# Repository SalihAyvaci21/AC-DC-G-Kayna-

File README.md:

# AC-DC Güç Kaynağı (115-250V AC -> 24V 5A)

Bu proje, 115-250V AC girişten 24V DC / 5A çıkış sağlayan bir **izole AC-DC güç kaynağı** devresidir. Yüksek güç yoğunluğu, güvenlik ve verimlilik odaklı olarak tasarlanmıştır.

## 📦 Özellikler

- **Giriş Gerilimi:** 115V - 250V AC
- **Çıkış Gerilimi:** 24V DC
- **Çıkış Akımı:** 5A (maksimum)
- **Topoloji:** Half-Bridge
- **Güvenlik ve Koruma Özellikleri:**
  - Yüksek sıcaklık koruması
  - Sigorta (Fuse)
  - Gaz Deşarj Tüpü (GDT)
  - EMI/RFI Giriş Filtresi
  - Aşırı Gerilim için Shutdown devresi (>27V)

## ⚡ Tasarım Bileşenleri

### Güç Faktörü Düzeltme (PFC)
- **Kontrolcü:** L6563
- **Fonksiyon:** Giriş AC sinyalini düzeltir ve 400V DC seviyesine çıkarır.

### Anahtarlama Aşaması
- **Topoloji:** Half-Bridge Konfigürasyonu
- **Kontrolcü:** L6599D
- **MOSFET’ler:** STP20H100
- **Trafo:** Yalıtımlı ve yüksek frekanslı dönüşüm için tasarlanmıştır.

### Çıkış Doğrultma ve Regülasyon
- **Çıkış Doğrultması:** STP20H100 MOSFET ile yüksek verimli doğrultma
- **Geribildirim (Feedback):**
  - **Optokuplör:** LTV-817S ile izole çıkış voltajı kontrolü
  - **Shutdown Devresi:** BC847 transistörü ile 27V üzerindeki çıkışlar için devreyi kapatma

## 🔥 Koruma ve Filtreleme

- **Giriş Filtresi:** EMI ve RFI bastırma için LC filtre
- **Sigorta ve GDT:** Aşırı akım ve yıldırım darbelerine karşı koruma
- **Yüksek Sıcaklık Koruması:** Termistör/NTC ile izleme

## 📐 PCB Özellikleri

- **Katman Sayısı:** 2 katman
- **İzole Alanlar:** Yüksek gerilim ve düşük gerilim bölgeleri arasında güvenli izolasyon
- **Soğutma:** Güç bileşenleri için yeterli soğutma alanı ve heatsink montaj noktaları

## 🛠 Kullanım

1. **Bağlantı:**
   - Giriş: L, N, Toprak terminalleri üzerinden AC şebekeye bağlayın.
   - Çıkış: +24V ve GND terminallerinden yük bağlantısı yapın.

2. **Çalıştırma:**
   - Güçü açmadan önce bağlantıları kontrol edin.
   - İlk açılışta boşta test yapılması önerilir.

3. **Koruma Devreleri:**
   - Çıkış aşırı gerilim durumunda (>27V) devre BC847 tarafından kapatılır.
   - Aşırı akım veya kısa devre durumunda sigorta atar.

## 📁 Dosyalar

- `AC-DC Güç Kaynağı.kicad_pro` – KiCAD proje dosyası
- `AC-DC Güç Kaynağı.kicad_sch` – Devre şeması
- `AC-DC Güç Kaynağı.kicad_pcb` – PCB yerleşim dosyası
- `BOM.csv` – Parça listesi
- `Fabrikation_Toolkit` – Üretim için gerber dosyaları

## ⚠️ Dikkat

> Yüksek gerilim içeren bu devre **hayati tehlike** arz eder. Lütfen yalnızca deneyimli kişiler tarafından çalıştırılsın.

## 📜 Lisans

Bu proje açık kaynaklıdır ve kişisel/akademik kullanım için ücretsizdir.

---

AC-DC Power Supply (115-250V AC -> 24V 5A)
This project is an isolated AC-DC power supply circuit that converts 115-250V AC input to 24V DC / 5A output. It is designed for high power density, safety, and efficiency.

📦 Features
Input Voltage: 115V - 250V AC

Output Voltage: 24V DC

Output Current: 5A (maximum)

Topology: Half-Bridge

Safety and Protection Features:

Over-temperature protection

Fuse protection

Gas Discharge Tube (GDT)

EMI/RFI input filter

Shutdown circuit for overvoltage (>27V)

⚡ Design Components
Power Factor Correction (PFC)
Controller: L6563

Function: Rectifies the AC input and boosts it to 400V DC.

Switching Stage
Topology: Half-Bridge Configuration

Controller: L6599D

MOSFETs: STP20H100

Transformer: Designed for isolated, high-frequency power conversion.

Output Rectification and Regulation
Output Rectification: High-efficiency rectification using STP20H100 MOSFET

Feedback:

Optocoupler: LTV-817S for isolated output voltage control

Shutdown Circuit: BC847 transistor to shut down the system when output exceeds 27V

🔥 Protection and Filtering
Input Filter: LC filter for EMI and RFI suppression

Fuse and GDT: Protection against overcurrent and lightning surges

Over-Temperature Protection: Monitored via Thermistor/NTC

📐 PCB Features
Layer Count: 2 layers

Isolation Zones: Safe separation between high-voltage and low-voltage areas

Cooling: Sufficient area for heatsinks and power component thermal management

🛠 Usage
Connections:

Input: Connect to AC mains via L, N, and Ground terminals.

Output: Connect the load to +24V and GND terminals.

Operation:

Verify all connections before powering on.

Recommended to perform no-load testing on initial startup.

Protection Circuits:

The BC847 transistor shuts down the system if the output voltage exceeds 27V.

The fuse blows in case of overcurrent or short circuit.

📁 Files
AC-DC Güç Kaynağı.kicad_pro – KiCAD project file

AC-DC Güç Kaynağı.kicad_sch – Schematic file

AC-DC Güç Kaynağı.kicad_pcb – PCB layout file

Bomlist.xlsx – Bill of Materials

Fabrikation_Toolkit – Gerber files for manufacturing

⚠️ Warning
This circuit involves high voltages and poses a risk of electric shock. It should only be operated by experienced individuals.

📜 License
This project is open-source and free for personal/academic use.

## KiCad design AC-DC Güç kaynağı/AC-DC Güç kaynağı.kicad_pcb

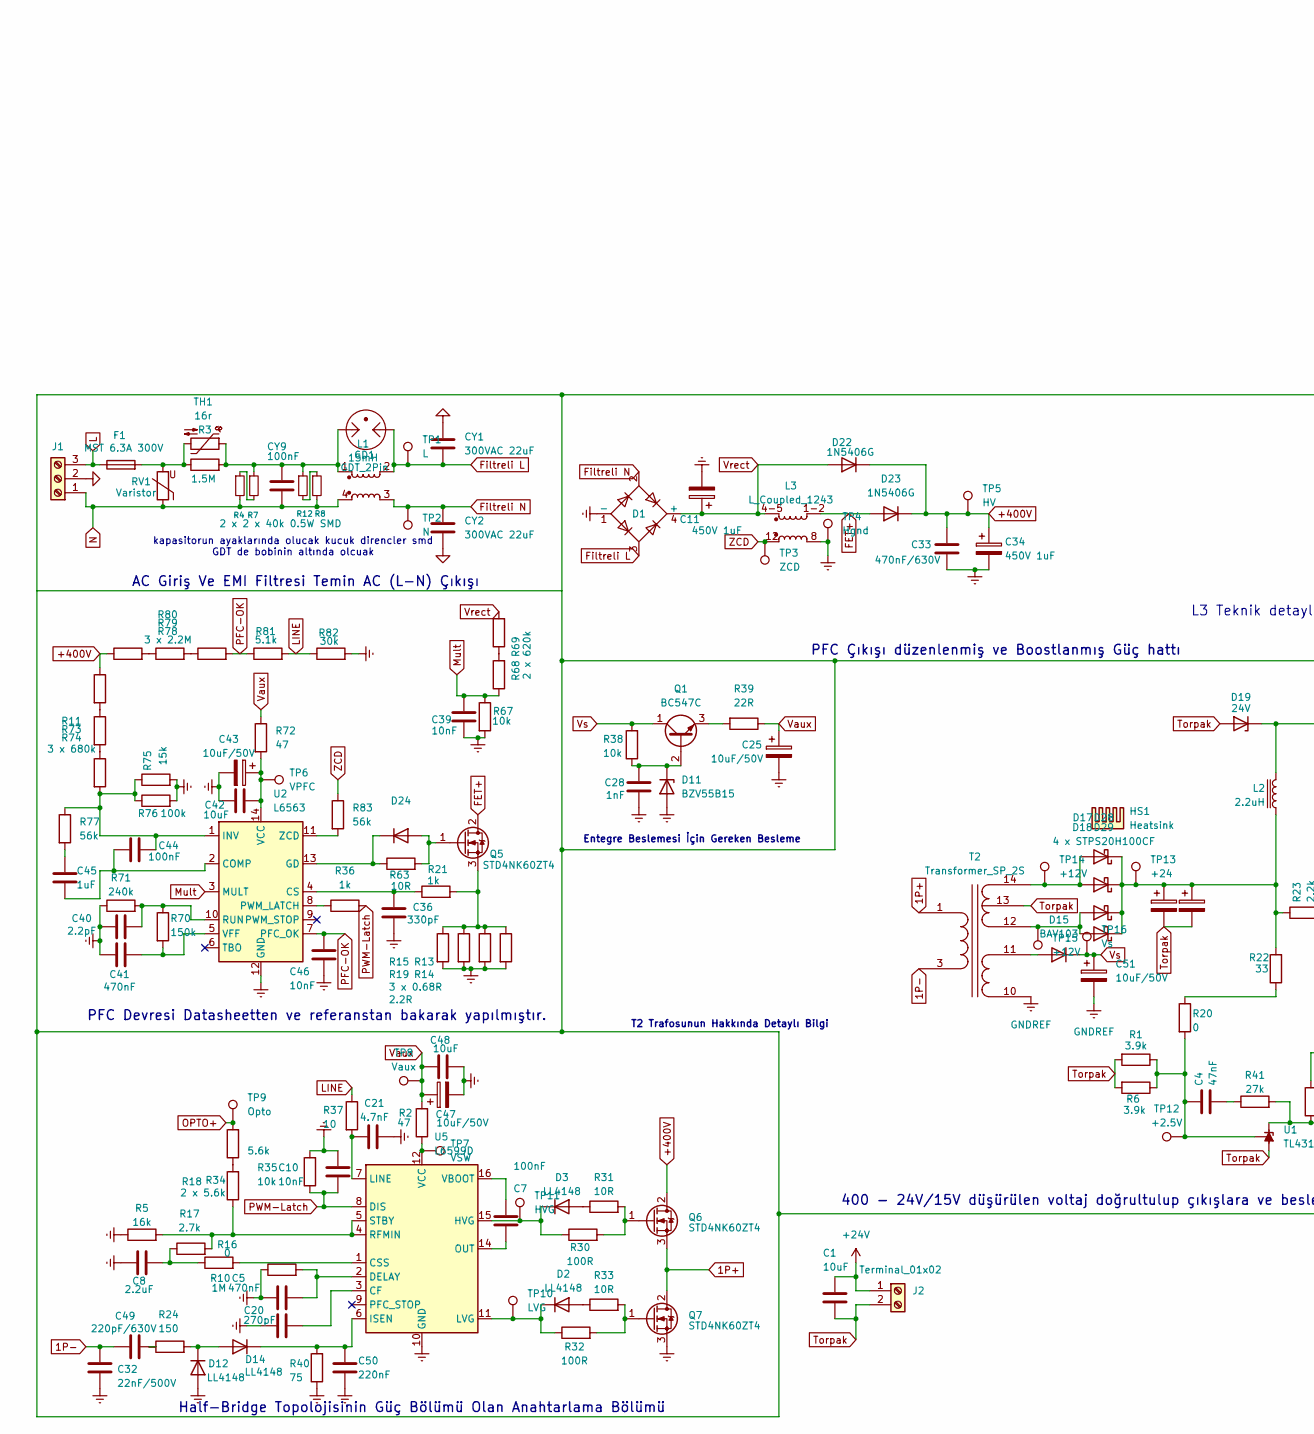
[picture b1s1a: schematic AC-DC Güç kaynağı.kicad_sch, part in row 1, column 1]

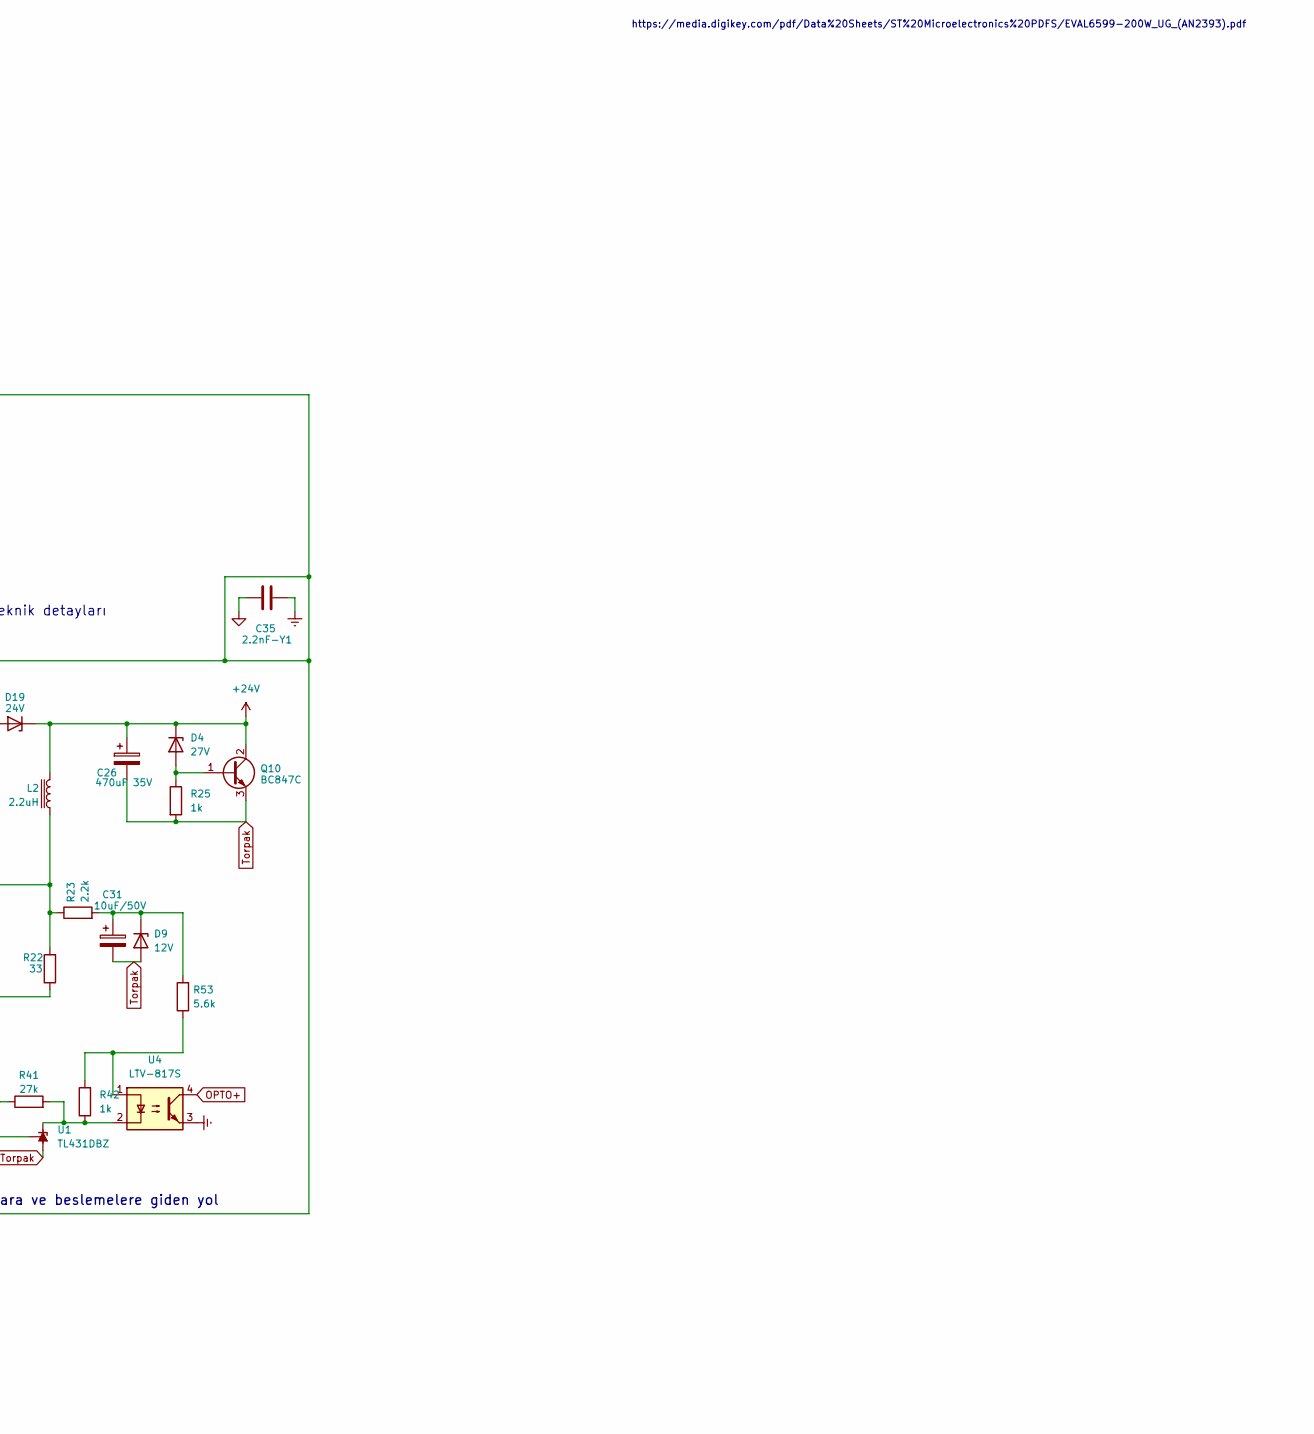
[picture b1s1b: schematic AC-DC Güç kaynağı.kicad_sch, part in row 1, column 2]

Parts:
C1, C42, C48: 10uF; C_1206_3216Metric_Pad1.33x1.80mm_HandSolder; Part Number CL31A106MBHNNNE
C4: 47nF; C_0603_1608Metric_Pad1.08x0.95mm_HandSolder; Part Number C0603C473K5RACTU
C5, C41: 470nF; C_0402_1005Metric_Pad0.74x0.62mm_HandSolder; Part Number GRM155R61H474KE11D
C7, C44: 100nF; C_0603_1608Metric_Pad1.08x0.95mm_HandSolder; Part Number 603-CC603KRX7R7BB104 Y
C8: 2.2uF; C_0603_1608Metric_Pad1.08x0.95mm_HandSolder; Part Number TMK107ABJ225KA-T
C10, C39, C46: 10nF; C_0603_1608Metric_Pad1.08x0.95mm_HandSolder; Part Number C0603C103K5RACTU
C11, C34: 450V 1uF; C_Radial_D8.0mm_H11.5mm_P3.50mm; Part Number UVR2W010MPD1TD
C14, C15, C26: 470uF 35V; C_Radial_D10.0mm_H16.0mm_P5.00mm; Part Number ESH477M035AH2AA
C20: 270pF; C_0603_1608Metric_Pad1.08x0.95mm_HandSolder; Part Number CL10C271JB81PNC
C21: 4.7nF; C_0603_1608Metric_Pad1.08x0.95mm_HandSolder; Part Number CC0603KRX7R9BB472
C25, C31, C43, C47, C51: 10uF/50V; C_Radial_D5.0mm_H7.0mm_P2.00mm; Part Number ESK106M050AC3AA
C28: 1nF; C_0603_1608Metric_Pad1.08x0.95mm_HandSolder; Part Number UMK107BJ105KA-T
C32: 22nF/500V; C_1206_3216Metric_Pad1.33x1.80mm_HandSolder; Part Number C1206C223KCRACAUTO
C33: 470nF/630V; C_Radial_D5.0mm_H7.0mm_P2.00mm; Part Number 46KI24700001K
C35: 2.2nF-Y1; C_Radial_D10.0mm_H16.0mm_P5.00mm; Part Number C751U222MWWDAAWL50
C36: 330pF; C_0603_1608Metric_Pad1.08x0.95mm_HandSolder; Part Number KGM15AR71E331KT
C40: 2.2pF; C_0603_1608Metric; Part Number CC0603BRNPO0BN2R2
C45: 1uF; C_0603_1608Metric_Pad1.08x0.95mm_HandSolder; Part Number UMK107BJ105KA-T
C49: 220pF/630V; C_0805_2012Metric; Part Number CC0805JRNPOZBN221
C50: 220nF; C_0805_2012Metric_Pad1.18x1.45mm_HandSolder; Part Number C0805C224K5RACTU
CY1, CY2: 300VAC 22uF; C_Radial_D8.0mm_H11.5mm_P3.50mm; Part Number DE2E3SA222MA3BX02F
CY9: 100nF; C_Rect_L18.0mm_W6.0mm_P15.00mm_FKS3_FKP3; Part Number 890324025017CS
D1: GBU8J; Diode_Bridge_Vishay_GBU; Part Number GBU8J
D2, D3, D12, D14, D24: LL4148; D_MiniMELF_Handsoldering; Part Number LL4148
D4: 27V; D_MiniMELF_Handsoldering; Part Number BZV55-B27,115
D9: 12V; D_MiniMELF_Handsoldering; Part Number BZV55-B12,115
D11: BZV55B15; D_MiniMELF_Handsoldering; Part Number BZV55-B15,115
D15: BAV103; D_MiniMELF_Handsoldering; Part Number BAV103
D17, D29: STPS20H100CF; TO-220-2_Horizontal_TabDown; Part Number MBR30200CT
D18: 2 x STPS20H100CF; TO-220-2_Horizontal_TabDown; Part Number MBR30200CT
D19: 24V; D_MiniMELF_Handsoldering; Part Number 771-BZV55-B24115
D22, D23: 1N5406G; D_DO-201AD_P12.70mm_Horizontal; Part Number 1N5406G
D28: 4 x STPS20H100CF; TO-220-2_Horizontal_TabDown; Part Number MBR30200CT
F1: MST 6.3A 300V; C_Rect_L9.0mm_W4.0mm_P7.50mm_MKT; Part Number RSTA 6.3 BULK
GD1: GDT_2Pin; Transformer_Wurth_WE-AGDT-EP7; Part Number 2003-35-SM-RPLF
HS1: Heatsink; Heatsink_125x35x50mm_3xFixationM3
J1: Screw_Terminal_01x03; TerminalBlock_Altech_AK300-3_P5.00mm
J2: Terminal_01x02; TerminalBlock_Altech_AK300-2_P5.00mm
L1: 15mH; EH24-3.0-02-1M2; Part Number EH24-3.0-02-1M2
L2: 2.2uH; Fuse_Littelfuse_372_D8.50mm; Part Number SBC3-2R2-602
L3: L_Coupled_1243
Q1: BC547C; TO-92Flat; Part Number BC547C
Q5, Q6, Q7: STD4NK60ZT4; TO-252-2; Part Number STD4NK60ZT4
Q10: BC847C; SOT-23-3; Part Number BC847C
R1, R6: 3.9k; R_1206_3216Metric_Pad1.30x1.75mm_HandSolder; Part Number RMCF1206FT3K90
R2, R72: 47; R_Axial_DIN0207_L6.3mm_D2.5mm_P10.16mm_Horizontal; Part Number FMP100JR-52-47R
R3: 1.5M; R_Axial_DIN0309_L9.0mm_D3.2mm_P12.70mm_Horizontal; Part Number ROX5SJ22R
R4: 2 x 2 x 40k 0.5W SMD; R_1206_3216Metric; Part Number RNCP1206FTD40K2TR-ND
R5: 16k; R_1206_3216Metric_Pad1.30x1.75mm_HandSolder; Part Number RC0805FR-0716KL
R7, R8, R12: 40k 0.5W SMD; R_1206_3216Metric; Part Number RNCP1206FTD40K2TR-ND
R10: 1M; R_0805_2012Metric_Pad1.20x1.40mm_HandSolder; Part Number RG2012P-105-D-T5
R11, R74: 680k; R_1206_3216Metric; Part Number RC1206FR-07680KL
R13: 2.2R; R_1206_3216Metric; Part Number RMCF1206FT2R20
R14, R15: 0.68R; R_1206_3216Metric; Part Number ERJ-8RQFR68V
R16, R20: 0; R_1206_3216Metric
R17: 2.7k; R_1206_3216Metric_Pad1.30x1.75mm_HandSolder; Part Number AC1206FR-072K7L
R18: 2 x 5.6k; C_1206_3216Metric_Pad1.33x1.80mm_HandSolder; Part Number CRGCQ1206F5K6
R19: 3 x 0.68R; R_1206_3216Metric; Part Number ERJ-8RQFR68V
R21, R25, R36, R42: 1k; R_1206_3216Metric_Pad1.30x1.75mm_HandSolder; Part Number RNCP1206FTD1K00
R22: 33; R_1206_3216Metric_Pad1.30x1.75mm_HandSolder; Part Number CRCW120633R0FKEAC
R23: 2.2k; R_1206_3216Metric_Pad1.30x1.75mm_HandSolder; Part Number CRGCQ1206F2K2
R24: 150; R_1206_3216Metric_Pad1.30x1.75mm_HandSolder; Part Number RC1206FR-07150RL
R30, R32: 100R; R_1206_3216Metric_Pad1.30x1.75mm_HandSolder; Part Number RC1206FR-07100RL
R31, R33, R63: 10R; R_1206_3216Metric_Pad1.30x1.75mm_HandSolder; Part Number RMCF1206FT10R0
R34, R53: 5.6k; R_1206_3216Metric_Pad1.30x1.75mm_HandSolder; Part Number CRGCQ1206F5K6
R35, R38, R67: 10k; R_1206_3216Metric_Pad1.30x1.75mm_HandSolder; Part Number RC1206FR-0715RL
R37: 10; R_1206_3216Metric_Pad1.30x1.75mm_HandSolder; Part Number RMCF1206FT10R0
R39: 22R; R_1206_3216Metric_Pad1.30x1.75mm_HandSolder; Part Number RC1206JR-0722RL
R40: 75; R_1206_3216Metric_Pad1.30x1.75mm_HandSolder; Part Number RMCF1206FT10R0
R41: 27k; R_1206_3216Metric_Pad1.30x1.75mm_HandSolder; Part Number RC1206JR-0727KL
R68: 620k; R_1206_3216Metric_Pad1.30x1.75mm_HandSolder; Part Number RC1206FR-07620KL
R69: 2 x 620k; R_1206_3216Metric; Part Number RC1206FR-07620KL
R70: 150k; R_1206_3216Metric_Pad1.30x1.75mm_HandSolder; Part Number RC1206FR-07150KL
R71: 240k; R_1206_3216Metric_Pad1.30x1.75mm_HandSolder; Part Number RC1206JR-07240KL
R73: 3 x 680k; R_1206_3216Metric; Part Number RC1206FR-07680KL
R75: 15k; R_1206_3216Metric_Pad1.30x1.75mm_HandSolder; Part Number RMCF1206JT15K0
R76: 100k; R_0805_2012Metric_Pad1.20x1.40mm_HandSolder; Part Number RG2012P-104-B-T5
R77, R83: 56k; R_1206_3216Metric_Pad1.30x1.75mm_HandSolder; Part Number RMCF1206JT56K0
R78, R80: 2.2M; R_1206_3216Metric; Part Number CRCW12062M20FKEA
R79: 3 x 2.2M; R_1206_3216Metric; Part Number CRCW12062M20FKEA
R81: 5.1k; R_1206_3216Metric_Pad1.30x1.75mm_HandSolder; Part Number RMCF1206JT5K10
R82: 30k; R_0805_2012Metric_Pad1.20x1.40mm_HandSolder; Part Number RMCF0805FT30K0
RV1: Varistor; RV_Disc_D7mm_W3.6mm_P5mm; Part Number B72210P2271K101
T2: Transformer_SP_2S; Trafo
TH1: 16r; CP_Radial_D5.0mm_P2.50mm; Part Number 954-10D2-07LD
TP1: L; TestPoint_Keystone_5000-5004_Miniature
TP2: N; TestPoint_Keystone_5000-5004_Miniature
TP3: ZCD; TestPoint_Keystone_5000-5004_Miniature
TP4: Hgnd; TestPoint_Keystone_5000-5004_Miniature
TP5: HV; TestPoint_Keystone_5000-5004_Miniature
TP6: VPFC; TestPoint_Keystone_5000-5004_Miniature
TP7: VSW; TestPoint_Keystone_5000-5004_Miniature
TP8: Vaux; TestPoint_Keystone_5000-5004_Miniature
TP9: Opto; TestPoint_Keystone_5000-5004_Miniature
TP10: LVG; TestPoint_Keystone_5000-5004_Miniature
TP11: HVG; TestPoint_Keystone_5000-5004_Miniature
TP12: +2.5V; TestPoint_Keystone_5000-5004_Miniature
TP13: +24; TestPoint_Keystone_5000-5004_Miniature
TP14, TP15: +12V; TestPoint_Keystone_5000-5004_Miniature
TP16: Vs; TestPoint_Keystone_5000-5004_Miniature
U1: TL431DBZ; SOT-23; Part Number TL431
U2: L6563; SOIC-14_3.9x8.7mm_P1.27mm; Part Number L6563
U4: LTV-817S; SMDIP-4_W9.53mm
U5: L6599D; SO-16_5.3x10.2mm_P1.27mm; Part Number L6599N

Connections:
1P+: Q6.3 (S), Q7.2 (D), T2.1 (IN+)
1P-: C32.2, C49.2, T2.3 (IN-)
+24V: C1.1, C26.1, D4.1 (K), D19.1 (K), J2.1, L2.2, Q10.2 (C)
+400V: C33.1, C34.1, D22.1 (K), D23.1 (K), L3.1, L3.2, Q6.2 (D), R11.1, R78.1, TP5.1; also elsewhere on the board
FET+: D23.2 (A), L3.1-2 (2), Q5.2 (D)
Filtreli L: CY1.2, D1.3, GD1.1, L1.2, TP1.1; also elsewhere on the board
Filtreli N: CY2.1, D1.2, L1.3, TP2.1; also elsewhere on the board
GND: C35.1, CY1.1, CY2.2, J1.2
GNDREF: C5.1, C8.1, C10.2, C11.2, C20.1, C21.2, C25.2, C28.2, C32.1, C33.2, C34.2, C35.2, C36.2, C39.2, C40.1, C41.1, C42.1, C43.2, C46.1, C47.2, C48.1, C50.1, C51.2, D1.1 (-), D11.2 (A), D12.2 (A), L3.8 (3), Q7.3 (S), R5.1, R10.1, R13.2, R14.2, R15.2, R19.2, R35.2, R40.1, R67.2, R71.1, R75.2, R76.2, R82.2, T2.10 (OUT2B), TP4.1, U2.12 (GND), U4.3, U5.10 (GND)
L: F1.1, J1.3
LINE: R37.1, R81.2, R82.1
Mult: C39.1, R67.1, R68.1, U2.3 (MULT)
N: CY9.2, J1.1, L1.4, R4.2, R8.2, RV1.1
unnamed: C4.1, R41.1
unnamed: C8.2, R16.1, R17.1
unnamed: C45.1, R77.2
unnamed: C49.1, R24.1
unnamed: CY9.1, GD1.3, L1.1, R3.2, R7.1, R12.1, TH1.1
unnamed: D2.2 (A), R33.1
unnamed 19: D2.1 (K), R32.1, TP10.1, U5.11 (LVG); also elsewhere on the board
unnamed: D3.2 (A), R31.1
unnamed 21: D3.1 (K), R30.1, TP11.1, U5.15 (HVG); also elsewhere on the board
unnamed: D4.2 (A), Q10.1 (B), R25.1
unnamed: C31.1, D9.1 (K), R23.2, R53.2
unnamed: C28.1, D11.1 (K), Q1.2 (B), R38.1
unnamed: D12.1 (K), D14.2 (A), R24.2
unnamed: C50.2, D14.1 (K), R40.2, U5.6 (ISEN)
unnamed: D15.2 (A), T2.11 (OUT2A)
unnamed 28: D17.2 (A), D28.2 (A), T2.14 (OUT1A), TP14.1; also elsewhere on the board
unnamed: C14.1, C15.1, D17.1 (K), D18.1 (K), D28.1 (K), D29.1 (K), L2.1, R22.2, R23.1, TP13.1
unnamed 30: D18.2 (A), D29.2 (A), T2.12 (OUT1B), TP15.1; also elsewhere on the board
unnamed: D24.2 (A), Q5.1 (G), R63.2
unnamed: D24.1 (K), R63.1, U2.13 (GD)
unnamed: F1.2, R3.1, RV1.2, TH1.2
unnamed: Q1.3 (E), R39.2
unnamed: Q5.3 (S), R13.1, R14.1, R15.1, R19.1, R21.2
unnamed: Q6.1 (G), R30.2, R31.2
unnamed: Q7.1 (G), R32.2, R33.2
unnamed: R4.1, R7.2
unnamed: R11.2, R73.1
unnamed: R8.1, R12.2
unnamed: R18.2, R34.1
unnamed: R20.1, R22.1
unnamed: R42.2, R53.1, U4.1
unnamed: R68.2, R69.1
unnamed: R73.2, R74.1
unnamed: R78.2, R79.1
unnamed: R79.2, R80.1
unnamed: R41.2, R42.1, U1.1 (K), U4.2
unnamed: C4.2, R1.1, R6.1, R20.2, TP12.1, U1.2 (REF)
unnamed: C44.2, C45.2, U2.2 (COMP)
unnamed: C36.1, R21.1, U2.4 (CS)
unnamed: C44.1, R74.2, R75.1, R76.1, R77.1, U2.1 (INV)
unnamed: R36.1, U2.8 (PWM_LATCH)
unnamed: C40.2, R70.1, R71.2, U2.10 (RUN)
unnamed 55: C42.2, C43.1, R72.2, TP6.1, U2.14 (VCC); also elsewhere on the board
unnamed: C41.2, R70.2, U2.5 (VFF)
unnamed: R83.2, U2.11 (ZCD)
unnamed: C20.2, U5.3 (CF)
unnamed: R16.2, U5.1 (CSS)
unnamed: C5.2, R10.2, U5.2 (DELAY)
unnamed: C21.1, R37.2, U5.7 (LINE)
unnamed: C7.2, U5.14 (OUT)
unnamed: R5.2, R17.2, R18.1, U5.4 (RFMIN), U5.5 (STBY)
unnamed: C7.1, U5.16 (VBOOT)
unnamed 65: R2.1, TP7.1, U5.12 (VCC); also elsewhere on the board
OPTO+: R34.2, TP9.1, U4.4; also elsewhere on the board
PFC-OK: C46.2, R80.2, R81.1, U2.7 (PFC_OK)
PWM-Latch: C10.1, R35.1, R36.2, U5.8 (DIS)
Torpak: C1.2, C14.2, C15.2, C26.2, C31.2, D9.2 (A), D19.2 (A), J2.2, Q10.3 (E), R1.2, R6.2, R25.2, T2.13 (PM), U1.3 (A)
Vaux: C25.1, C47.1, C48.2, R2.2, R39.1, R72.1, TP8.1
Vrect: C11.1, D1.4 (+), D22.2 (A), L3.4, L3.4-5 (1), L3.5, R69.2
Vs: C51.1, D15.1 (K), Q1.1 (C), R38.2, TP16.1; also elsewhere on the board
ZCD: L3.12 (4), R83.1, TP3.1

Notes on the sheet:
kapasitorun ayaklarında olucak kucuk direncler smd GDT de bobinin altında olcuak
PFC Devresi Datasheetten ve referanstan bakarak yapılmıştır.
PFC Çıkışı düzenlenmiş ve Boostlanmış Güç hattı
https://media.digikey.com/pdf/Data%20Sheets/ST%20Microelectronics%20PDFS/EVAL6599-200W_UG_(AN2393).pdf
Half-Bridge Topolojisinin Güç Bölümü Olan Anahtarlama Bölümü
L3 Teknik detayları
AC Giriş Ve EMI Filtresi Temin AC (L-N) Çıkışı
Entegre Beslemesi İçin Gereken Besleme
400 - 24V/15V düşürülen voltaj doğrultulup çıkışlara ve beslemelere giden yol
T2 Trafosunun Hakkında Detaylı Bilgi

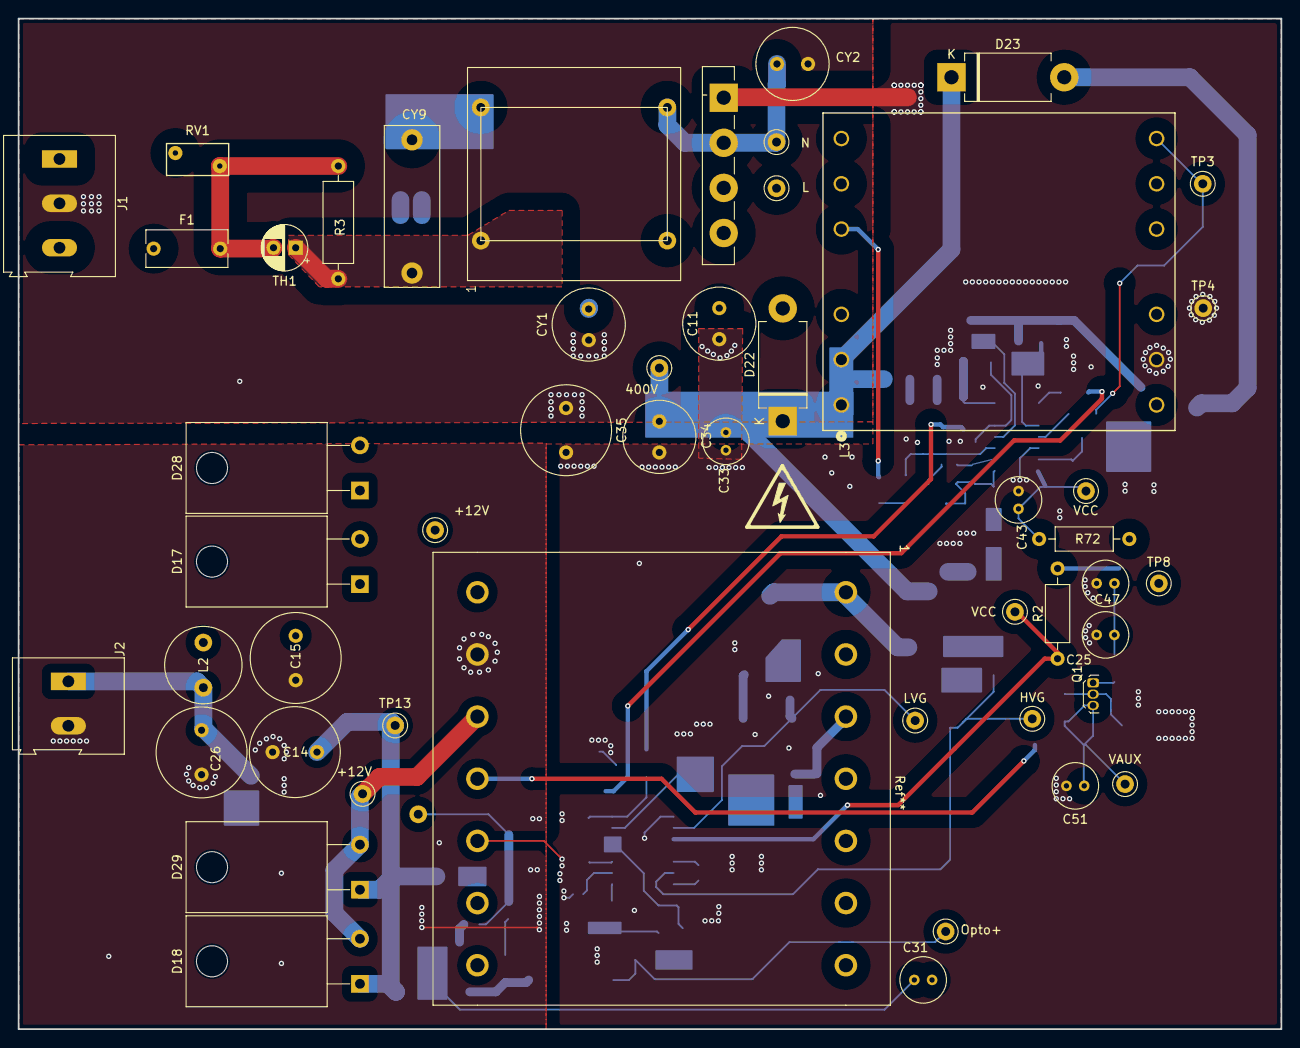
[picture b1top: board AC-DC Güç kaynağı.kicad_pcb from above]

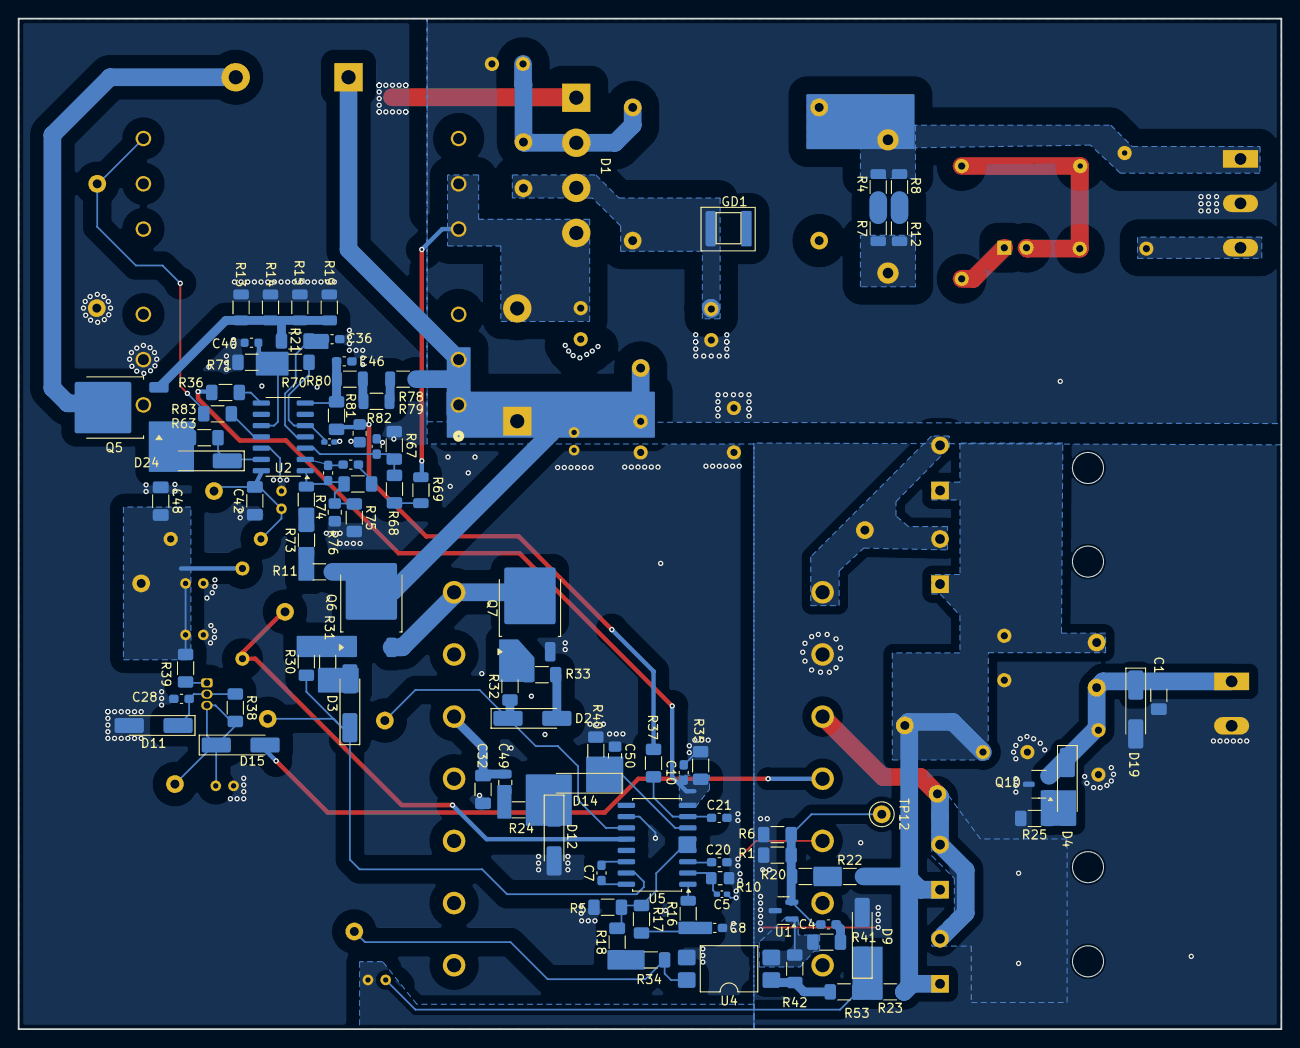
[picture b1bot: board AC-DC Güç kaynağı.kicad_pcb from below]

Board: 2 copper layers, 142.2 x 113.8 mm, 144 parts (94 on the bottom side), 74 nets.

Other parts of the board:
400V: HV; TestPoint_Keystone_5000-5004_Miniature
+12V, +12V#2: +12V; TestPoint_Keystone_5000-5004_Miniature
HVG: HVG; TestPoint_Keystone_5000-5004_Miniature
L: L; TestPoint_Keystone_5000-5004_Miniature
LVG: LVG; TestPoint_Keystone_5000-5004_Miniature
N: N; TestPoint_Keystone_5000-5004_Miniature
Opto+: Opto; TestPoint_Keystone_5000-5004_Miniature
VAUX: Vs; TestPoint_Keystone_5000-5004_Miniature
VCC: VSW; TestPoint_Keystone_5000-5004_Miniature
VCC#2: VPFC; TestPoint_Keystone_5000-5004_Miniature

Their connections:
+400V: 400V.1; also elsewhere on the board
Filtreli L: L.1; also elsewhere on the board
Filtreli N: N.1; also elsewhere on the board
unnamed 19: LVG.1; also elsewhere on the board
unnamed 21: HVG.1; also elsewhere on the board
unnamed 28: +12V#2.1; also elsewhere on the board
unnamed 30: +12V.1; also elsewhere on the board
unnamed 55: VCC#2.1; also elsewhere on the board
unnamed 65: VCC.1; also elsewhere on the board
OPTO+: Opto+.1; also elsewhere on the board
Vs: VAUX.1; also elsewhere on the board

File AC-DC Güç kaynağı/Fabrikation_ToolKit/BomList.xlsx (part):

'Reference' | 'Value' | 'Qty' | 'Part Number' | 'supplier part number' | 'supplier' | 'Footprint'
'C1,C42,C48' | '10uF' | '3' | 'CL31A106MBHNNNE' | '187-CL31A106MBHNNNE' | mouser' | 'Capacitor_SMD:C_1206_3216Metric_Pad1.33x1.80mm_HandSolder'
'C4' | '47nF' | '1' | ' C0603C473K5RACTU' | '80-C0603C473K5R' | mouser' | 'Capacitor_SMD:C_0603_1608Metric_Pad1.08x0.95mm_HandSolder'
'C5,C41' | '470nF' | '2' | ' GRM155R61H474KE11D' | '81-GRM155R61H474KE1D' | mouser' | 'Capacitor_SMD:C_0402_1005Metric_Pad0.74x0.62mm_HandSolder'
'C7,C44' | '100nF' | '2' | '603-CC603KRX7R7BB104 Y' | 'CC0603KRX7R7BB104' | mouser' | 'Capacitor_SMD:C_0603_1608Metric_Pad1.08x0.95mm_HandSolder'
'C8' | '2.2uF' | '1' | 'TMK107ABJ225KA-T' | '963-TMK107ABJ225KA-T ' | mouser' | 'Capacitor_SMD:C_0603_1608Metric_Pad1.08x0.95mm_HandSolder'
'C10,C39,C46' | '10nF' | '3' | 'C0603C103K5RACTU' | '80-C0603C103K5R' | mouser' | 'Capacitor_SMD:C_0603_1608Metric_Pad1.08x0.95mm_HandSolder'
'C11,C34' | '450V 1uF' | '2' | ' UVR2W010MPD1TD' | '647-UVR2W010MPD1TD' | mouser' | 'Capacitor_THT:C_Radial_D8.0mm_H11.5mm_P3.50mm'
'C14,C15,C26' | '470uF 35V' | '3' | ' ESH477M035AH2AA' | '80-ESH477M035AH2AA' | mouser' | 'Capacitor_THT:C_Radial_D10.0mm_H16.0mm_P5.00mm'
'C20' | '270pF' | '1' | 'CL10C271JB81PNC' | '187-CL10C271JB81PNC' | mouser' | 'Capacitor_SMD:C_0603_1608Metric_Pad1.08x0.95mm_HandSolder'
'C21' | '4.7nF' | '1' | 'CC0603KRX7R9BB472' | '603-C0603KRX7R9BB472' | mouser' | 'Capacitor_SMD:C_0603_1608Metric_Pad1.08x0.95mm_HandSolder'
'C25,C31,C43,C47,C51' | '10uF/50V' | '5' | ' ESK106M050AC3AA' | '80-ESK106M050AC3AA ' | mouser' | 'Capacitor_THT:C_Radial_D5.0mm_H7.0mm_P2.00mm'
'C28' | '1nF' | '1' | 'UMK107BJ105KA-T' | '963-UMK107BJ105KA-T' | mouser' | 'Capacitor_SMD:C_0603_1608Metric_Pad1.08x0.95mm_HandSolder'
'C32' | '22nF/500V' | '1' | 'C1206C223KCRACAUTO' | '80-C1206C223KCRAUTO' | mouser' | 'Capacitor_SMD:C_1206_3216Metric_Pad1.33x1.80mm_HandSolder'
'C33' | '470nF/630V' | '1' | '46KI24700001K' | '80-R46KI24700001K' | mouser' | 'Capacitor_THT:C_Radial_D5.0mm_H7.0mm_P2.00mm'
'C35' | '2.2nF-Y1' | '1' | 'C751U222MWWDAAWL50' | '80-C751U222MWWDAWL50' | mouser' | 'Capacitor_THT:C_Radial_D10.0mm_H16.0mm_P5.00mm'
'C36' | '330pF' | '1' | ' KGM15AR71E331KT' | '581-KGM15AR71E331KT' | mouser' | 'Capacitor_SMD:C_0603_1608Metric_Pad1.08x0.95mm_HandSolder'
'C40' | '2.2pF' | '1' | ' CC0603BRNPO0BN2R2' | '603-CC0603BNPO0BN2R2' | mouser' | 'Capacitor_SMD:C_0603_1608Metric'
'C45' | '1uF' | '1' | 'UMK107BJ105KA-T' | '963-UMK107BJ105KA-T' | mouser' | 'Capacitor_SMD:C_0603_1608Metric_Pad1.08x0.95mm_HandSolder'
'C49' | '220pF/630V' | '1' | 'CC0805JRNPOZBN221' | '603-CC805JRNPOZBN221' | mouser' | 'Capacitor_SMD:C_0805_2012Metric'
'C50' | '220nF' | '1' | ' C0805C224K5RACTU' | '80-C0805C224K5R' | mouser' | 'Capacitor_SMD:C_0805_2012Metric_Pad1.18x1.45mm_HandSolder'
'CY1,CY2' | '300VAC 22uF' | '2' | 'DE2E3SA222MA3BX02F' | '490-DE2E3SA222MA3BX02F-ND' | mouser' | 'Capacitor_THT:C_Radial_D8.0mm_H11.5mm_P3.50mm'
'CY9' | '100nF' | '1' | '890324025017CS' | '710-890324025017CS' | mouser' | 'Capacitor_THT:C_Rect_L18.0mm_W6.0mm_P15.00mm_FKS3_FKP3'
'D1' | 'GBU8J' | '1' | 'GBU8J' | '637-GBU8J' | mouser' | 'Diode_THT:Diode_Bridge_Vishay_GBU'
'D2,D3,D12,D14,D24' | 'LL4148' | '5' | 'LL4148' | '637-LL4148' | mouser' | 'Diode_SMD:D_MiniMELF_Handsoldering'
'D4' | '27V' | '1' | 'BZV55-B27,115' | '771-BZV55-B27115' | mouser' | 'Diode_SMD:D_MiniMELF_Handsoldering'
'D9' | '12V' | '1' | 'BZV55-B12,115' | '771-BZV55-B12115' | mouser' | 'Diode_SMD:D_MiniMELF_Handsoldering'
'D11' | 'BZV55B15' | '1' | 'BZV55-B15,115' | '771-BZV55-B15-T/R' | mouser' | 'Diode_SMD:D_MiniMELF_Handsoldering'
'D15' | 'BAV103' | '1' | 'BAV103' | '512-BAV103' | mouser' | 'Diode_SMD:D_MiniMELF_Handsoldering'
'D17,D29' | 'STPS20H100CF' | '2' | 'MBR30200CT' | '637-MBR30200CT' | mouser' | 'Package_TO_SOT_THT:TO-220-2_Horizontal_TabDown'
'D18' | '2 x STPS20H100CF' | '1' | 'MBR30200CT' | '637-MBR30200CT' | mouser' | 'Package_TO_SOT_THT:TO-220-2_Horizontal_TabDown'
'D19' | '24V' | '1' | '771-BZV55-B24115' | '771-BZV55-B24115' | mouser' | 'Diode_SMD:D_MiniMELF_Handsoldering'
'D22,D23' | '1N5406G' | '2' | '1N5406G' | '863-1N5406G' | mouser' | 'Diode_THT:D_DO-201AD_P12.70mm_Horizontal'
'D28' | '4 x STPS20H100CF' | '1' | 'MBR30200CT' | '637-MBR30200CT' | mouser' | 'Package_TO_SOT_THT:TO-220-2_Horizontal_TabDown'
'F1' | 'MST 6.3A 300V' | '1' | 'RSTA 6.3 BULK' | '530-RSTA6.3BULK' | mouser' | 'Capacitor_THT:C_Rect_L9.0mm_W4.0mm_P7.50mm_MKT'
'GD1' | 'GDT_2Pin' | '1' | '2003-35-SM-RPLF' | '652-2003-35-SM-RPLF' | mouser' | 'Transformer_SMD:Transformer_Wurth_WE-AGDT-EP7'
'HS1' | 'Heatsink' | '1' | '' | '' | mouser' | 'Heatsink:Heatsink_125x35x50mm_3xFixationM3'
'J1' | 'Screw_Terminal_01x03' | '1' | '' | '' | mouser' | 'TerminalBlock:TerminalBlock_Altech_AK300-3_P5.00mm'
'J2' | 'Terminal_01x02' | '1' | '' | '' | mouser' | 'TerminalBlock:TerminalBlock_Altech_AK300-2_P5.00mm'
'L1' | '15mH' | '1' | 'EH24-3.0-02-1M2' | '631-EH24-3.0-02-1M2' | mouser' | 'Library:EH24-3.0-02-1M2'
'L2' | '2.2uH' | '1' | 'SBC3-2R2-602' | '80-SBC3-2R2-602' | mouser' | 'Fuse:Fuse_Littelfuse_372_D8.50mm'
'L3' | 'L_Coupled_1243' | '1' | '' | '' | mouser' | ''
'Q1' | 'BC547C' | '1' | 'BC547C' | '637-BC547C' | mouser' | 'Package_TO_SOT_THT:TO-92Flat'
'Q5,Q6,Q7' | 'STD4NK60ZT4' | '3' | 'STD4NK60ZT4' | '511-STD4NK60Z' | mouser' | 'Package_TO_SOT_SMD:TO-252-2'
'Q10' | 'BC847C' | '1' | 'BC847C' | '637-BC847C' | mouser' | 'Package_TO_SOT_SMD:SOT-23-3'
'R1,R6' | '3.9k' | '2' | 'RMCF1206FT3K90' | '708-RMCF1206FT3K90' | mouser' | 'Resistor_SMD:R_1206_3216Metric_Pad1.30x1.75mm_HandSolder'
'R2,R72' | '47' | '2' | 'FMP100JR-52-47R' | '603-FMP100JR-52-47R' | mouser' | 'Resistor_THT:R_Axial_DIN0207_L6.3mm_D2.5mm_P10.16mm_Horizontal'
'R3' | '1.5M' | '1' | 'ROX5SJ22R' | '279-ROX5SJ22R' | mouser' | 'Resistor_THT:R_Axial_DIN0309_L9.0mm_D3.2mm_P12.70mm_Horizontal'
'R4' | '2 x 2 x 40k 0.5W SMD' | '1' | 'RNCP1206FTD40K2TR-ND' | 'RNCP1206FTD40K2TR-ND' | mouser' | 'Resistor_SMD:R_1206_3216Metric'
'R5' | '16k' | '1' | 'RC0805FR-0716KL' | '603-RC0805FR-0716KL' | mouser' | 'Resistor_SMD:R_1206_3216Metric_Pad1.30x1.75mm_HandSolder'
'R7,R8,R12' | '40k 0.5W SMD' | '3' | 'RNCP1206FTD40K2TR-ND' | 'RNCP1206FTD40K2TR-ND' | mouser' | 'Resistor_SMD:R_1206_3216Metric'
'R10' | '1M' | '1' | 'RG2012P-105-D-T5' | '754-RG2012P-105DT5' | mouser' | 'Resistor_SMD:R_0805_2012Metric_Pad1.20x1.40mm_HandSolder'
'R11,R74' | '680k' | '2' | 'RC1206FR-07680KL' | '603-RC1206FR-07680KL' | mouser' | 'Resistor_SMD:R_1206_3216Metric'
'R13' | '2.2R' | '1' | 'RMCF1206FT2R20' | '708-RMCF1206FT2R20' | mouser' | 'Resistor_SMD:R_1206_3216Metric'
'R14,R15' | '0.68R' | '2' | 'ERJ-8RQFR68V' | '667-ERJ-8RQFR68V' | mouser' | 'Resistor_SMD:R_1206_3216Metric'
'R16,R20' | '0' | '2' | '' | '' | mouser' | 'Resistor_SMD:R_1206_3216Metric'
'R17' | '2.7k' | '1' | 'AC1206FR-072K7L' | '603-AC1206FR-072K7L' | mouser' | 'Resistor_SMD:R_1206_3216Metric_Pad1.30x1.75mm_HandSolder'
'R18' | '2 x 5.6k' | '1' | 'CRGCQ1206F5K6' | '279-CRGCQ1206F5K6' | mouser' | 'Capacitor_SMD:C_1206_3216Metric_Pad1.33x1.80mm_HandSolder'
'R19' | '3 x 0.68R' | '1' | 'ERJ-8RQFR68V' | '667-ERJ-8RQFR68V' | mouser' | 'Resistor_SMD:R_1206_3216Metric'
'R21,R25,R36,R42' | '1k' | '4' | ' RNCP1206FTD1K00' | '708-RNCP1206FTD1K00' | mouser' | 'Resistor_SMD:R_1206_3216Metric_Pad1.30x1.75mm_HandSolder'
'R22' | '33' | '1' | ' CRCW120633R0FKEAC' | '71-CRCW120633R0FKEAC' | mouser' | 'Resistor_SMD:R_1206_3216Metric_Pad1.30x1.75mm_HandSolder'
'R23' | '2.2k' | '1' | 'CRGCQ1206F2K2' | '279-CRGCQ1206F2K2' | mouser' | 'Resistor_SMD:R_1206_3216Metric_Pad1.30x1.75mm_HandSolder'
'R24' | '150' | '1' | 'RC1206FR-07150RL' | '603-RC1206FR-07150RL' | mouser' | 'Resistor_SMD:R_1206_3216Metric_Pad1.30x1.75mm_HandSolder'
'R30,R32' | '100R' | '2' | 'RC1206FR-07100RL' | '603-RC1206FR-07100RL' | mouser' | 'Resistor_SMD:R_1206_3216Metric_Pad1.30x1.75mm_HandSolder'
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
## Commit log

2025-07-18 README.md
